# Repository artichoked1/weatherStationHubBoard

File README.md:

# Weather Station Hub Board

This is a hub board that collects data from multiple sensors via RS485 and sends it to a server via LoRaWAN.
d

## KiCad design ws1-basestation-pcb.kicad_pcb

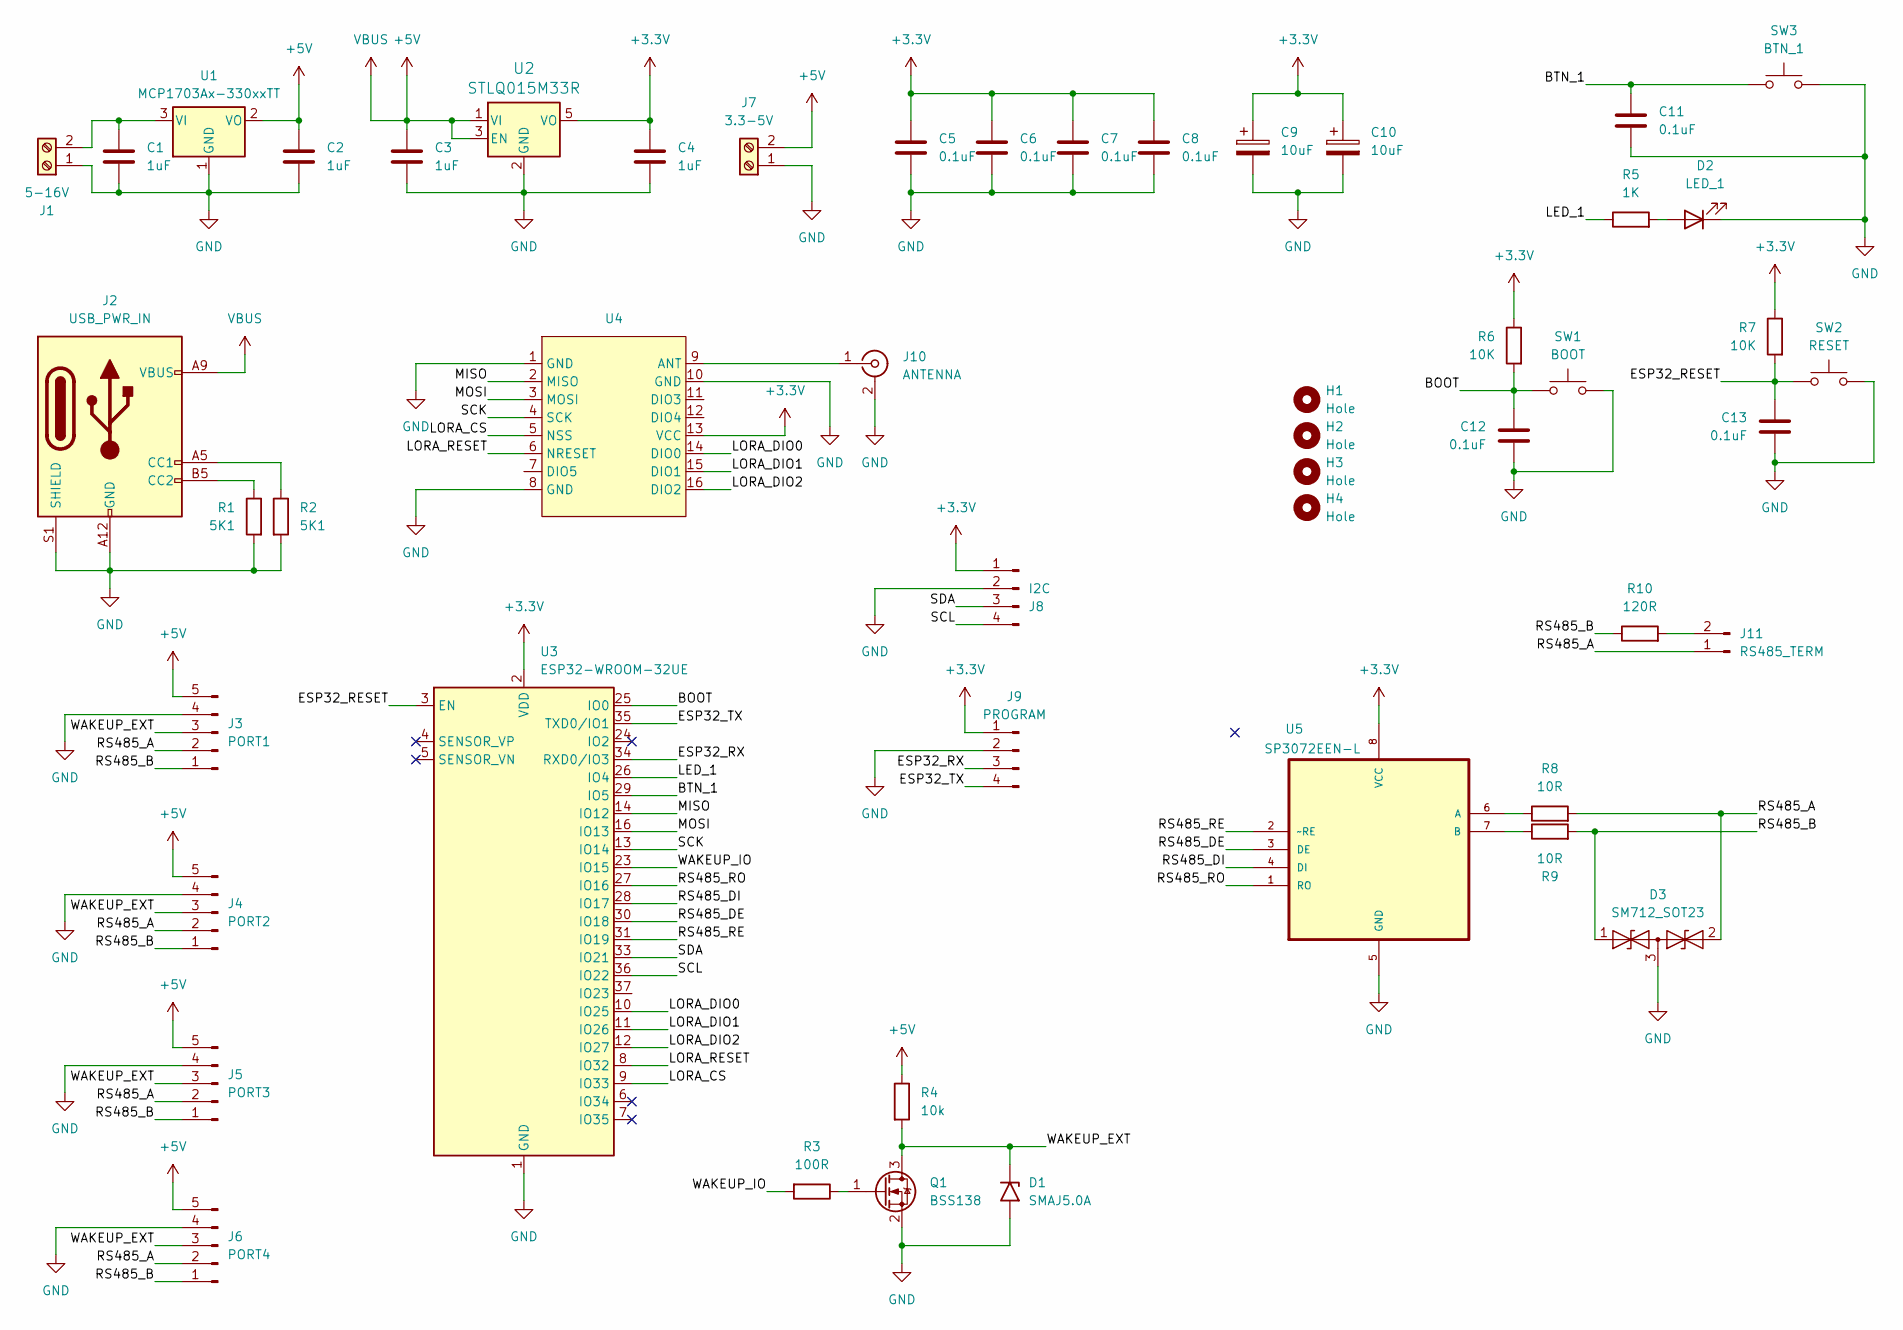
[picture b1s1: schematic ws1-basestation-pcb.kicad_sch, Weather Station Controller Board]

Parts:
C1, C2, C3, C4: 1uF; C_Disc_D4.7mm_W2.5mm_P5.00mm
C5, C6, C7, C8, C11, C12, C13: 0.1uF; C_Disc_D4.7mm_W2.5mm_P5.00mm
C9, C10: 10uF; CP_Radial_D5.0mm_P2.50mm
D1: SMAJ5.0A; D_SMA
D2: LED_1; LED_D3.0mm_Horizontal_O3.81mm_Z2.0mm
D3: SM712_SOT23; SOT-23
H1, H2, H3, H4: Hole; MountingHole_3.5mm
J1: 5-16V; TerminalBlock_bornier-2_P5.08mm
J2: USB_PWR_IN; USB_C_Receptacle_GCT_USB4125-xx-x-0190_6P_TopMnt_Horizontal
J3: PORT1; JST_XH_B5B-XH-A_1x05_P2.50mm_Vertical
J4: PORT2; JST_XH_B5B-XH-A_1x05_P2.50mm_Vertical
J5: PORT3; JST_XH_B5B-XH-A_1x05_P2.50mm_Vertical
J6: PORT4; JST_XH_B5B-XH-A_1x05_P2.50mm_Vertical
J7: 3.3-5V; TerminalBlock_bornier-2_P5.08mm
J8: I2C; PinHeader_1x04_P2.54mm_Vertical
J9: PROGRAM; PinHeader_1x04_P2.54mm_Vertical
J10: ANTENNA; SMA_Amphenol_901-143_Horizontal
J11: RS485_TERM; PinHeader_1x02_P2.54mm_Horizontal
Q1: BSS138; SOT-23
R1, R2: 5K1; R_Axial_DIN0207_L6.3mm_D2.5mm_P10.16mm_Horizontal
R3: 100R; R_Axial_DIN0207_L6.3mm_D2.5mm_P10.16mm_Horizontal
R4: 10k; R_Axial_DIN0207_L6.3mm_D2.5mm_P10.16mm_Horizontal
R5: 1K; R_Axial_DIN0207_L6.3mm_D2.5mm_P10.16mm_Horizontal
R6, R7: 10K; R_Axial_DIN0207_L6.3mm_D2.5mm_P10.16mm_Horizontal
R8, R9: 10R; R_Axial_DIN0207_L6.3mm_D2.5mm_P10.16mm_Horizontal
R10: 120R; R_Axial_DIN0207_L6.3mm_D2.5mm_P10.16mm_Horizontal
SW1: BOOT; SW_1-1825027-1
SW2: RESET; SW_1-1825027-1
SW3: BTN_1; SW_1-1825027-1
U1: MCP1703Ax-330xxTT; SOT-23
U2: STLQ015M33R; SOT-23-5_HandSoldering
U3: ESP32-WROOM-32UE
U4: HOPERF_RFM9XW_SMD
U5: SP3072EEN-L; SOIC-8_3.9x4.9mm_P1.27mm; MPN SP3072EEN-L

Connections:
+3.3V: C4.1, C5.1, C6.1, C7.1, C8.1, C9.1, C10.1, J8.1, J9.1, R6.1, R7.1, U2.5 (VO), U3.2 (VDD), U4.13 (VCC), U5.8 (VCC)
+5V: C2.1, C3.1, J2.A9 (VBUS), J2.B9 (VBUS), J3.5, J4.5, J5.5, J6.5, J7.2, R4.1, U1.2 (VO), U2.1 (VI), U2.3 (EN)
/BOOT: C12.1, R6.2, SW1.2, U3.25 (IO0)
/BTN_1: C11.1, SW3.1, U3.29 (IO5)
/ESP32_RESET: C13.1, R7.2, SW2.2, U3.3 (EN)
/ESP32_RX: J9.3, U3.34 (RXD0/IO3)
/ESP32_TX: J9.4, U3.35 (TXD0/IO1)
/LED_1: R5.1, U3.26 (IO4)
/LORA_CS: U3.9 (IO33), U4.5 (NSS)
/LORA_DIO0: U3.10 (IO25), U4.14 (DIO0)
/LORA_DIO1: U3.11 (IO26), U4.15 (DIO1)
/LORA_DIO2: U3.12 (IO27), U4.16 (DIO2)
/LORA_RESET: U3.8 (IO32), U4.6 (NRESET)
/MISO: U3.14 (IO12), U4.2 (MISO)
/MOSI: U3.16 (IO13), U4.3 (MOSI)
/RS485_A: D3.2 (A2), J3.2, J4.2, J5.2, J6.2, J11.1, R8.2
/RS485_B: D3.1 (A1), J3.1, J4.1, J5.1, J6.1, R9.2, R10.1
/RS485_DE: U3.30 (IO18), U5.3 (DE)
/RS485_DI: U3.28 (IO17), U5.4 (DI)
/RS485_RE: U3.31 (IO19), U5.2 (~RE)
/RS485_RO: U3.27 (IO16), U5.1 (RO)
/SCK: U3.13 (IO14), U4.4 (SCK)
/SCL: J8.4, U3.36 (IO22)
/SDA: J8.3, U3.33 (IO21)
/WAKEUP_EXT: D1.1 (A1), J3.3, J4.3, J5.3, J6.3, Q1.3 (D), R4.2
/WAKEUP_IO: R3.2, U3.23 (IO15)
GND: C1.2, C2.2, C3.2, C4.2, C5.2, C6.2, C7.2, C8.2, C9.2, C10.2, C11.2, C12.2, C13.2, D1.2 (A2), D2.1 (K), D3.3 (common), J1.1, J2.A12 (GND), J2.B12 (GND), J2.S1 (SHIELD), J3.4, J4.4, J5.4, J6.4, J7.1, J8.2, J9.2, J10.2 (Ext), Q1.2 (S), R1.2, R2.2, SW1.1, SW2.1, SW3.2, U1.1 (GND), U2.2 (GND), U3.1 (GND), U3.15 (GND), U3.38 (GND), U3.39 (GND), U4.1 (GND), U4.8 (GND), U4.10 (GND), U5.5 (GND)
unnamed: D2.2 (A), R5.2
unnamed: C1.1, J1.2, U1.3 (VI)
unnamed: J2.A5 (CC1), R2.1
unnamed: J2.B5 (CC2), R1.1
unnamed: J10.1 (In), U4.9 (ANT)
unnamed: J11.2, R10.2
unnamed: Q1.1 (G), R3.1
unnamed: R8.1, U5.6 (A)
unnamed: R9.1, U5.7 (B)

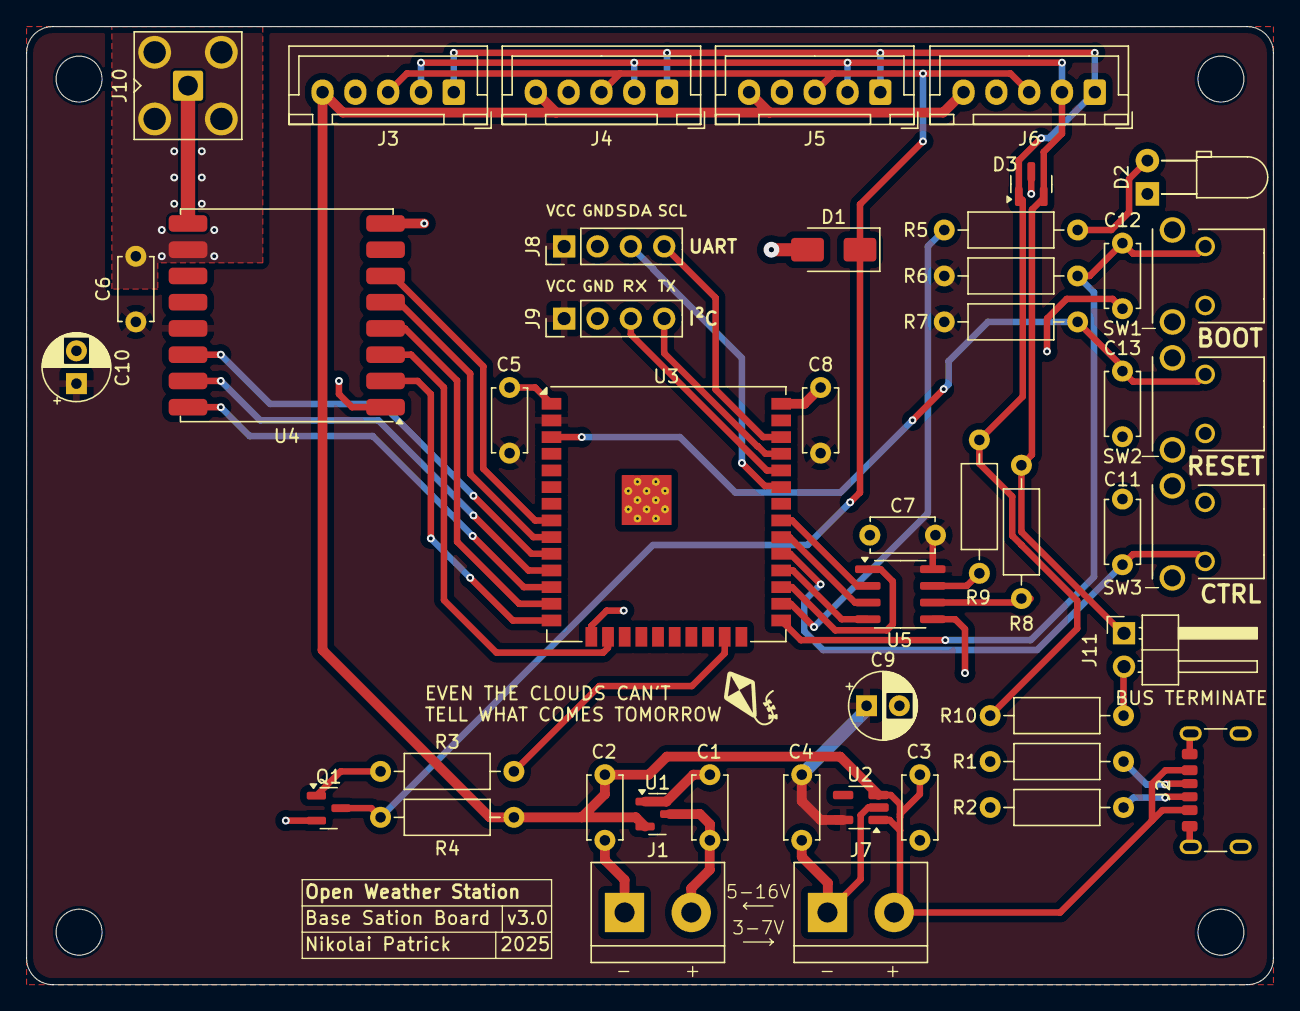
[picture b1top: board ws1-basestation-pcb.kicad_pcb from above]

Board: 2 copper layers, 95.0 x 73.0 mm, 50 parts (0 on the bottom side), 36 nets.

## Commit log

2025-04-28 add readme
2025-04-28 test
2025-04-30 changeport connectors, move lora module, and impedance-match antenna
2025-05-04 rename project files
